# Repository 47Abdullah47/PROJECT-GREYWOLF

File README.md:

<h1 align="center">﷽</h1>
<h1 align="center">
<font size="6"><b>🛦 X-26 GREYWOLF PT-1</b></font>
</h1><br>

<h4 align="center">
  <b>The First High-Performance Experimental 12S EDF Prototype of the YF-26 GREYWOLF Program</b>
</h4>
<p align="center">
  <a href="#technical-specifications">Technical Specifications</a> •
  <a href="#visual-looks">Visual Looks</a> •
  <a href="#airframe-materials-list">Materials</a> •
  <a href="#electronics--propulsion-system">Electronics Strategy</a> •
  <a href="#system-wiring-diagram">Wiring Diagram</a> •
  <a href="#success-criteria--flight-goals">Flight Goals</a> •
  <a href="#assembly-guide">Assembly</a> •
  <a href="#credits">Credits</a> •
  <a href="#license">License</a>
</p>
<br>

> **Project Status:** Prototype 1 (PT-1) Engineering, Aerodynamic Simulation & CAD Phase Complete  
> **CAD Platform:** Autodesk Fusion 360  
> **Development Pipeline:** [Hack Club Stasis Dashboard](https://stasis.hackclub.com/dashboard/projects/cmnfqlx3300nv01qimu2rgsk3)  
> **Design Time Investment:** 50+ Hours of High-Fidelity Surface Modeling  
> **Source CAD File:** 💾 [Download Massive Fusion 360 (.f3d) Assembly via Google Drive](https://github.com/47Abdullah47/X-26-GREYWOLF-PT-1/blob/Main-Project-PT-1/SOURCE%20FILE.md)

---

## Technical Specifications

The **X-26 GREYWOLF PT-1** is a high-speed, scratch-built experimental scale RC jet aircraft. It is engineered around an advanced integrated propulsion duct system and a multi-axis high-lift control surface layout to study level transonic airflow behaviors, intake fluid dynamics, and low-altitude flight stability.

* **Total Length of Aircraft:** 1.3 - 1.5 meters
* **Total Height of Aircraft (without landing Gear):** 0.3m (~30cm)
* **Fuselage Hull Height:** 0.1m (~11cm) *(Optimized to wrap tightly around the internal engine bay)*
* **Wingspan:** ~1.0 meter
* **Wing Area:** ~0.1 m²
* **Total Control Channels:** 6 Channels (2x Flaps, 2x Ailerons, 2x Stabilators)
* **Aerodynamic Design & Fluid Optimization:** Validated via rigorous computational fluid dynamics (CFD) steady-state solver testing run at a 20 m/s airspeed vector, establishing a baseline cruise lift coefficient ($C_L$) of 0.0141 and an ultra-low geometric shape drag coefficient ($C_D$) of 0.0018.
* **Special Intake Engineering:** Features a custom-modeled internal S-Duct intake routing system designed to stabilize incoming air turbulence and manage static pressure gradients under high mass flows.
* **Performance Profile:** Estimated empty airframe weight ranges from 2.0 to 3.0 kg. Powered by a high-output 12S electric ducted fan producing between 4.0 - 5.0 kg of static thrust, yielding a >1:1 thrust-to-weight ratio for a flight envelope targeting 100 - 110 mph.
* **Short-Runway (STOL) Takeoff Speeds:**
  * *Unladen / Light Test Rig (3.5 kg):* 21.3 m/s - 23.0 m/s (~76 km/h)
  * *Maximum Operational Testing Payload (4.5 kg):* 24.6 m/s - 26.1 m/s (~94 km/h)
* **Control Surface Mixing:** Implements symmetrical **Flaperon** mixing, deflecting both flaps and main ailerons together at takeoff. This transforms **41.5% of the total wing area ($372.68\text{ cm}^2$)** into an active camber-shifting high-lift surface, rocketing the maximum takeoff lift coefficient ($C_{L_{\text{max}}}$) to approximately 0.165.

*Note: The structural frames, nose cone mechanics, and intake paths are modeled as completely independent components within the source assembly to allow for modular fabrication and fast battery bay accessibility.*

---

## Visual Looks

<h3 align="center"><b>CAD Model Overview</b></h3>
<p align="center">

  <a href="https://youtu.be/b9qI-MGt7ME"><b>A demonstration of the actuation of Control Surfaces</b></a>

</p>

<h3 align="center"><b>High-Fidelity Rendered Visuals</b></h3>

> **Design Note on Airframe Influence:** > The X-26 Greywolf airframe merges generation-defining design aspects. It utilizes high-efficiency forward intakes inspired by the F-22 Raptor, twin vertical stabilizing surfaces and an exhaust layout optimized similarly to the F-35 Lightning II, and an internal structural distribution derived from the F-16 Fighting Falcon. 

---

## Airframe Materials List

The structural framework utilizes a lightweight, high-strength composite prototyping approach to handle structural stress thresholds while maximizing the power-to-weight ratio:

1. **Depron Foam / High-Speed LW-PLA:** Used for the aerodynamic outer skin contours, wing surfacing, and lightweight internal fuselage formers.
2. **Carbon Fiber Spars & Rods (3mm):** Integrated directly into high-stress structural joints, serving as the main wing load spars, tail pivot shafts, and longitudinal fuselage stiffeners.
3. **Aircraft-Grade Plywood:** Selected for high-vibration structural hardpoints, specifically the main 12S EDF engine mount and landing gear mounting plates.

---

## Electronics & Propulsion Strategy

The PT-1's avionics bay is engineered to safely sustain high continuous current loads. Comprehensive component sourcing, unit prices, and specific funding breakdowns are tracked in the dedicated [Bill of Materials Guide](BOM.md).

### Power Architecture Summary:
1. **High-Voltage Power Loop:** Two independent 6S LiPo battery packs (5200mAh - 5900mAh) are linked in **series** using a heavy-duty **QS-8 Anti-Spark Series Harness** to deliver a unified 12S nominal voltage supply (44.4V nominal / 50.4V peak) directly to the ESC.
2. **Propulsion Drive Loop:** High-gauge phase leads feed directly from the Hobbywing 100A V2 ESC to the brushless motor inside the 80mm fan shroud.
3. **Low-Voltage Signal Loop:** Signal power to the 10-channel FlySky receiver steps down cleanly via the ESC's integrated Battery Eliminator Circuit (BEC) lines.
4. **Control Surface Actuation:** Symmetrical servos are linked across the receiver layout using heavy-duty Y-harness extensions to maintain precise dual-aileron, dual-flap, and stabilator mechanical sync.

---

## System Wiring Diagram

The PT-1 utilizes a clean point-to-point wiring schematic optimized for minimal line resistance and spatial balance within the narrow fuselage ribbing. 

---

## Success Criteria & Flight Goals

To rigorously evaluate the airframe engineering and telemetry code, the testing program focuses on three definitive goals:
1. **Aerodynamic Validation:** Confirm stable, level cruise tracking at a 20 m/s airspeed vector to ground-truth our baseline steady-state CFD dataset.
2. **STOL Performance:** Verify short-runway rotation and lift-off performance using the 41.5% trailing-edge flaperon configuration under incremental payload loads.

---

## Assembly Guide
The proper assembling procedure of the aircraft is as follows:-
<h3><b>THE SPINE</b></h3>
<p>The airduct of the plane has two major and very important roles in the aircraft, it serves as <b>THE SPINE</b> of the plane and the **The duct that** asissts the airflow.
It being <b>The Spine</b>  of the airplane, it will be the one hosting the airframe ribs.
</p>

<h3><b>Air-Frame Ribs Placement</b></h3>
<p>  The cuted out airframed ribs are slided onto the air duct, which is the spine of the aircraft. 
</p>

 <h3><b> First Skin Placement</b></h3>
 After sliding on the Airframe ribs onto the Airduct..The lower fuselage skin is mounted onto the airframe ribs.

<h3><b>Mounting Side panels</b></h3>
After mounting lower skin panel of the fuselage..the side skin panels are mounted onto the Airframe.

<h3><b>Adding support</b></h3>
3mm Carbon fibre rods are slided into the premade holes in airframes..the goal is to provide the airframe with a good tensile and torsion strength.
Also one of the rear support ribs are slided onto the carbin fibre rod for attatching to the main spine and be a part of the barrier against crushing G-force..Also the remaining side panels of the fuselage are mounted onto the rear support ribs.

<h3><b>Mounting Inner Skin Panels</b></h3>
Rear Inner skin panels are also mounted onto the rear support ribs.

<h3><b>Construction of the Stabs(stabilators)</b></h3>
The stab's construction is simple yet requires carefullness regarding the building process...The root aerofoil is mounted on the outer edges of the stab.

After mounting the root aerofoil on the root edge of lower skin panel of the stab...
the upper skin panel is mounted onto the root aerofoil and the corresponding outer edges of the lower skin panel....

After sucessfully mounting skin panels and the root aerfoil to eachother...the pivot rod is slided into the premade hole in the root aero foil.... 
The stabilators are done being built.

<h3><b>Mounting The Remaining Skin Panels</b></h3>
The remaing rear lower skin panels of the fuselage are also mounted onto the rear support ribs of the Fuselage..with the side skin panels supporting it.

After completing mounting the rear side of lower skin panels..The rear skin panels of the upper skin are also mounted onto the rear support ribs....

After mounting first rear skin panel of the upper skin...the second pair of skin panels are mounted onto the Airframe ribs...these two skin panels are directly sitting above the main propulsion unit of the UAV..

The side long skin panels are also mounted onto the Airframe ribs..these skin panels cover up the most of the Fuselage's upper skin....

The front upper skin panels of the Fuselage are mounted onto the front Airframe Ribs of the Airframe with the remaining upper side panels of the Airframe....the Cavity behind these panels is the space of the removeable panels that allow accessing the inner components of the Aircraft without needing to rip-apart the skin of the Aircraft.

A brief 3d view for the Construction described so far.
<video src="https://github.com/user-attachments/assets/6bf46d65-2bc3-4322-bec0-19ca2d736067" autoplay loop muted width="100%"></video>

<h3><b>Mounting Engine Nozzle</b></h3>
The Engine nozzle is consisted of 5 panels..the first three panels are mounted onto the correspeonding edges of the Inner side panels and Upper skin panels....

The fourth skin panel of the Engine nozzle is mounted onto the corresponding edges of the lower skin panel and onto the corresponding side edges of the second and thord side panels of the engnine side panels.

the last panel is the exhuast panel of the engine bay section, this can be replaced by a servo operated variable engine nozzle too, which is not the part of current development.

<h3><b>Installing the Nose ribs, nose panels, And completing the Fuselage</b></h3>
The Nose is installed by folowing a complex assembling procedure, the Battery block itself serves as a support, The two nose ribs are slided onto the carbon fibre rods, In this way the base of the nose is installed onto the Fuselage.

The lower nose skin panels are installed onto the assembled Structure of the Nose

After mounting the lower panels the side Skin panels are mounted onto the so far assembled nose strucutre.

After that The next Nose Rib is installed by three support brigdes,

After adding the next rib, the corresponding side Skin panels are mounted.

After mounting Side skin panels, the corresponding upper Skin panel is mounted 

after that, another Rib is added to the structure, and corresponding remaining side skin panels are mounted on, 

After that the last remaining upper skin panel is mounted.

THE DIVERGERS:-
The divergers are mounted on the tip of the lower intake Skin panel, Its purpose is to separate the low speed skin air from the high speed air,

After All of this process the Construction of the Fuselage is done.

<h3><b>Assembling the V-tails</b></h3>
The Ribs of the tails are mounted onto the one side of the Skins of the tail, 

After joining the Ribs with one skin, The other skin is mounted onto the ribs and the other skin,

Just like this the second tail is constructed, After joining skins and the ribs of the tail, the lower base root panel is mounted, sealing the whole structure,

After that carbon fibre support rods are slided into pre-built holes in the root panel,

This support rib is situated perpendicular to the actuator support of the STABS, its purpose is to lockin the Carbon fibre support Rods of the V-tails.

The Tails are slided into the Fuselage, Like This, (this is the inner view removing the outer skin panel from the vie)

And with that The V-tails are fused into the Fuselage.

<h3><b>Assembling the Wings</b></h3>
The front Ribs of the wing are fitted into the slots of the front spar, 

after fitting the ribs into the front spar, the main spar is slided onto the sleves of the ribs

After fitting the Main spar, the sleves of the Rear Ribs are slided into the main spar

the edge support ribs are then slided into gltye rear sleves of the rear ribs,

after that the Rear spar is fitted into the joint intersections made into the ribs and the spar.

After This step the Main Root aerofoil bulkhead is slided into the spar sleves to complete the structure of the removeable wings.

The two 5mm Carbon fibre rods are then slided into the holes and then locked using the collars inside the wings, so that the wings can be slides on and removed for easy transportation. 

The upper skin of 2mm depron is mounted onto the complex wing structure.

After mounting the upper depron skin, the lower depron skin is mounted to complete tge aerodynamic shape of the wing, also for servo fittings, there are pre cutout parts on the lower depron skin

And after that the sides of the wing, the "WING TIPS" are mounted on,

After mounting the wing tips, the
control surfaces "Flaps and Ailerons" are mounted onto the hinges that are fitted into the hinge support ribs, And the removeable wings are Completed

Now the 6mm wings' support bulkhead is installed into the airframe ribs and with the support rib similar to the root rib of the wing, enabling those two 5mm carbon fibre rods to be slided into the airframe,

This is how the Wing is installed, the carbon fibre rods are tightened up with the help of collars,

<h3><b>The Actuation Mechansim of Flaps and Ailerons</b></h3>
This is where the servos for Flaps and Ailerons go into the eing, and the actuation mechanism is shown perfectly below👇 

<h3><b>The Actuation Mechansim of the Stabilators</b></h3>
This is how the pushrods for the actuation of Stabilators reside,
a collar is installed onto the 3mm carbon fibre rod, that is connected to the stabilator, and the pushrod is used to rotate the collar which in turn, turns the rod, actuationg the stabilator

This is where the servo resides into the rear support ribs.

<h3><b>The Residence of The ESC</b></h3>
The esc is placed in the lower storage bay in the Airframe, that is near the lower skin panel and below the peak before dice of the Airduct.

<h3><b>Placement of the EDF</b></h3>
The EDF is placed onto the mounting brackets installed between the Airframe ribs, And is directly placed into the Airduct with the mouth directky attached to the exit of the Airduct to prevent any Airfeed Loss.
(The Air duct is hidden for a bteer view on the placement of the EDF)

<H3><B>Placement of the Reciever</B></H3>
The reciever/flight controller is placed in the upper storage bay that is direclty below the mid upper skin panel, The reason is to prevent any electrical noise from interfering with the reciver/FC, and for extending the antennas into carbon fibre free sections to prevent signal screening.

<h3>Placement of the batteries </h3>
The two 6s lipo packs are slided into the battery block that is also serving as the lower spine of the nose section, The block has cutouts on the upper sides to allow the wires to flow into the rear section of the UAV, and tye charging wires to be accessed easily.

<h4><b>THE END</b></h4>
And the Assembling process comes to an end. The product should,.must look like this

---

## Credits

* **My Father:** A seasoned professional in his aviation field who taught me the foundational mechanics of aircraft design, and inspired me to build this dream.
* **My Brother:** The catalyst who challenged me to test my limits, stepped up my design thinking, and introduced me to the open-source hardware community.
* **Hack Club Blueprint & Stasis Teams:** For establishing a development pipeline that empowers teenagers to scale up their hardware engineering skills and bring complex concepts to life.

---

## License

This project is open-source and licensed under the terms of the MIT License.

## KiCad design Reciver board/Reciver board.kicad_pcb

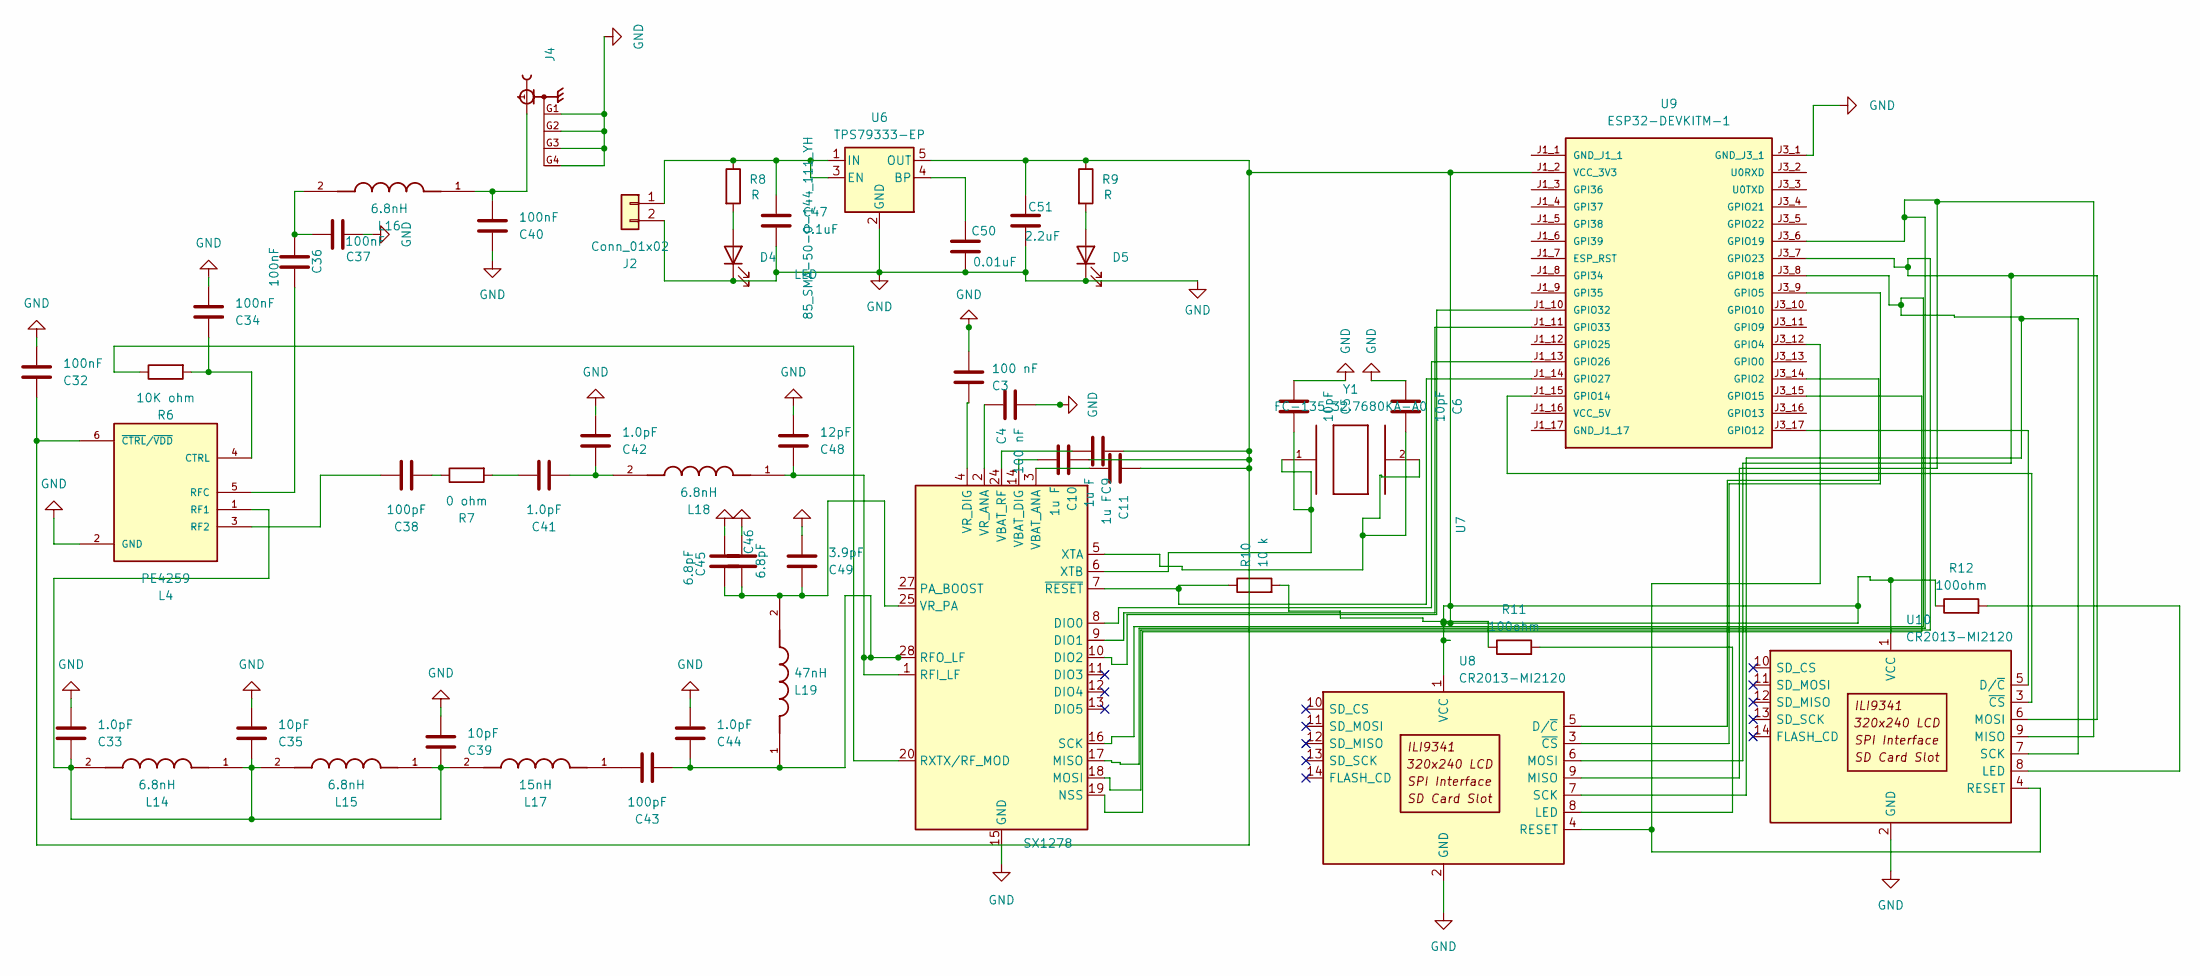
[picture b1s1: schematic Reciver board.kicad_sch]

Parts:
C3, C4: 100 nF; C_0201_0603Metric
C5: 10pF; C_0402_1005Metric
C6, C35, C39: 10pF; C_0201_0603Metric
C9, C10, C11: 1u F; C_0201_0603Metric
C32, C34, C36, C37, C40: 100nF; C_0201_0603Metric
C33, C41, C42, C44: 1.0pF; C_0201_0603Metric
C38, C43: 100pF; C_0201_0603Metric
C45, C46: 6.8pF; C_0201_0603Metric
C47: 0.1uF; C_0201_0603Metric
C48: 12pF; C_0201_0603Metric
C49: 3.9pF; C_0201_0603Metric
C50: 0.01uF; C_0201_0603Metric
C51: 2.2uF; C_0201_0603Metric
D4, D5: LED; LED_0805_2012Metric
J2: Conn_01x02; PinHeader_1x02_P2.54mm_Vertical
J4: 85_SMA-50-0-144_111_YH; HUBER_SUHNER_85_SMA-50-0-144_111_YH; PARTREV a
L4: PE4259; SOT65P215X110-6N
L14, L15, L16, L18: 6.8nH; IND_LQP03HQ10NH02D; PARTREV N/A
L17: 15nH; IND_LQP03HQ10NH02D; PARTREV N/A
L19: 47nH; IND_LQP03HQ10NH02D; PARTREV N/A
R6: 10K ohm; R_0201_0603Metric
R7: 0 ohm; R_0201_0603Metric
R8, R9: R; LED_0805_2012Metric
R10: 10 k; R_0201_0603Metric
R11, R12: 100ohm; R_0201_0603Metric
U6: TPS79333-EP; SOT-23-5
U7: SX1278; QFN-28-1EP_6x6mm_P0.65mm_EP4.8x4.8mm
U8, U10: CR2013-MI2120
U9: ESP32-DEVKITM-1; MODULE_ESP32-DEVKITM-1; PARTREV 1.0
Y1: FC-135_32.7680KA-A0; XTAL_FC-135_32.7680KA-A0

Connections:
GND: C3.2, C4.2, C5.1, C6.1, C32.2, C33.2, C34.2, C35.2, C37.2, C39.2, C40.1, C42.2, C44.2, C45.2, C46.2, C47.2, C48.2, C49.2, C50.2, C51.2, D4.1 (K), D5.1 (K), J2.2, J4.G1, J4.G2, J4.G3, J4.G4, L4.2 (GND), U6.2 (GND), U7.15 (GND), U7.21 (GND), U7.22 (GND), U7.23 (GND), U7.26 (GND), U7.29 (GND), U8.2 (GND), U9.J3_1 (GND_J3_1), U10.2 (GND)
unnamed: C36.2, C37.1, L16.2
unnamed: C38.2, R7.1
unnamed: C40.2, J4.1, L16.1
unnamed: C41.1, R7.2
unnamed: C41.2, C42.1, L18.2
unnamed: C43.1, L17.1
unnamed: D4.2 (A), R8.2
unnamed: D5.2 (A), R9.2
unnamed: C47.1, J2.1, R8.1, U6.1 (IN), U6.3 (EN)
unnamed: C34.1, L4.4 (CTRL), R6.2
unnamed: C33.1, C35.1, C39.1, L4.1 (RF1), L14.1, L14.2, L15.1, L15.2, L17.2
unnamed: C38.1, L4.3 (RF2)
unnamed: C36.1, L4.5 (RFC)
unnamed: C9.1, C10.1, C11.1, C32.1, C51.1, L4.6 (~CTRL/~VDD), R9.1, R10.2, R11.1, R12.1, U6.5 (OUT), U8.1 (VCC), U9.J1_2 (VCC_3V3), U10.1 (VCC)
unnamed: C50.1, U6.4 (BP)
unnamed: U7.8 (DIO0), U9.J1_13 (GPIO26)
unnamed: U7.9 (DIO1), U9.J1_11 (GPIO33)
unnamed: U7.10 (DIO2), U9.J1_10 (GPIO32)
unnamed: U7.19 (NSS), U9.J3_15 (GPIO15)
unnamed: C43.2, C44.1, C48.1, L18.1, L19.1, U7.1 (RFI_LF), U7.28 (RFO_LF)
unnamed: R6.1, U7.20 (RXTX/RF_MOD)
unnamed: C11.2, U7.3 (VBAT_ANA)
unnamed: C10.2, U7.14 (VBAT_DIG)
unnamed: C9.2, U7.24 (VBAT_RF)
unnamed: C4.1, U7.2 (VR_ANA)
unnamed: C3.1, U7.4 (VR_DIG)
unnamed: C45.1, C46.1, C49.1, L19.2, U7.25 (VR_PA)
unnamed: C6.2, U7.5 (XTA), Y1.2
unnamed: C5.2, U7.6 (XTB), Y1.1
unnamed: R10.1, U7.7 (~RESET), U9.J1_14 (GPIO27)
unnamed: U8.5 (D/~C), U9.J3_14 (GPIO2)
unnamed: R11.2, U8.8 (LED)
unnamed: U8.3 (~CS), U9.J3_9 (GPIO5)
unnamed: U9.J3_17 (GPIO12), U10.5 (D/~C)
unnamed: R12.2, U10.8 (LED)
unnamed: U7.17 (MISO), U8.9 (MISO), U9.J3_6 (GPIO19), U10.9 (MISO)
unnamed: U7.18 (MOSI), U8.6 (MOSI), U9.J3_7 (GPIO23), U10.6 (MOSI)
unnamed: U8.4 (RESET), U9.J3_12 (GPIO4), U10.4 (RESET)
unnamed: U7.16 (SCK), U8.7 (SCK), U9.J3_8 (GPIO18), U10.7 (SCK)
unnamed: U9.J1_15 (GPIO14), U10.3 (~CS)

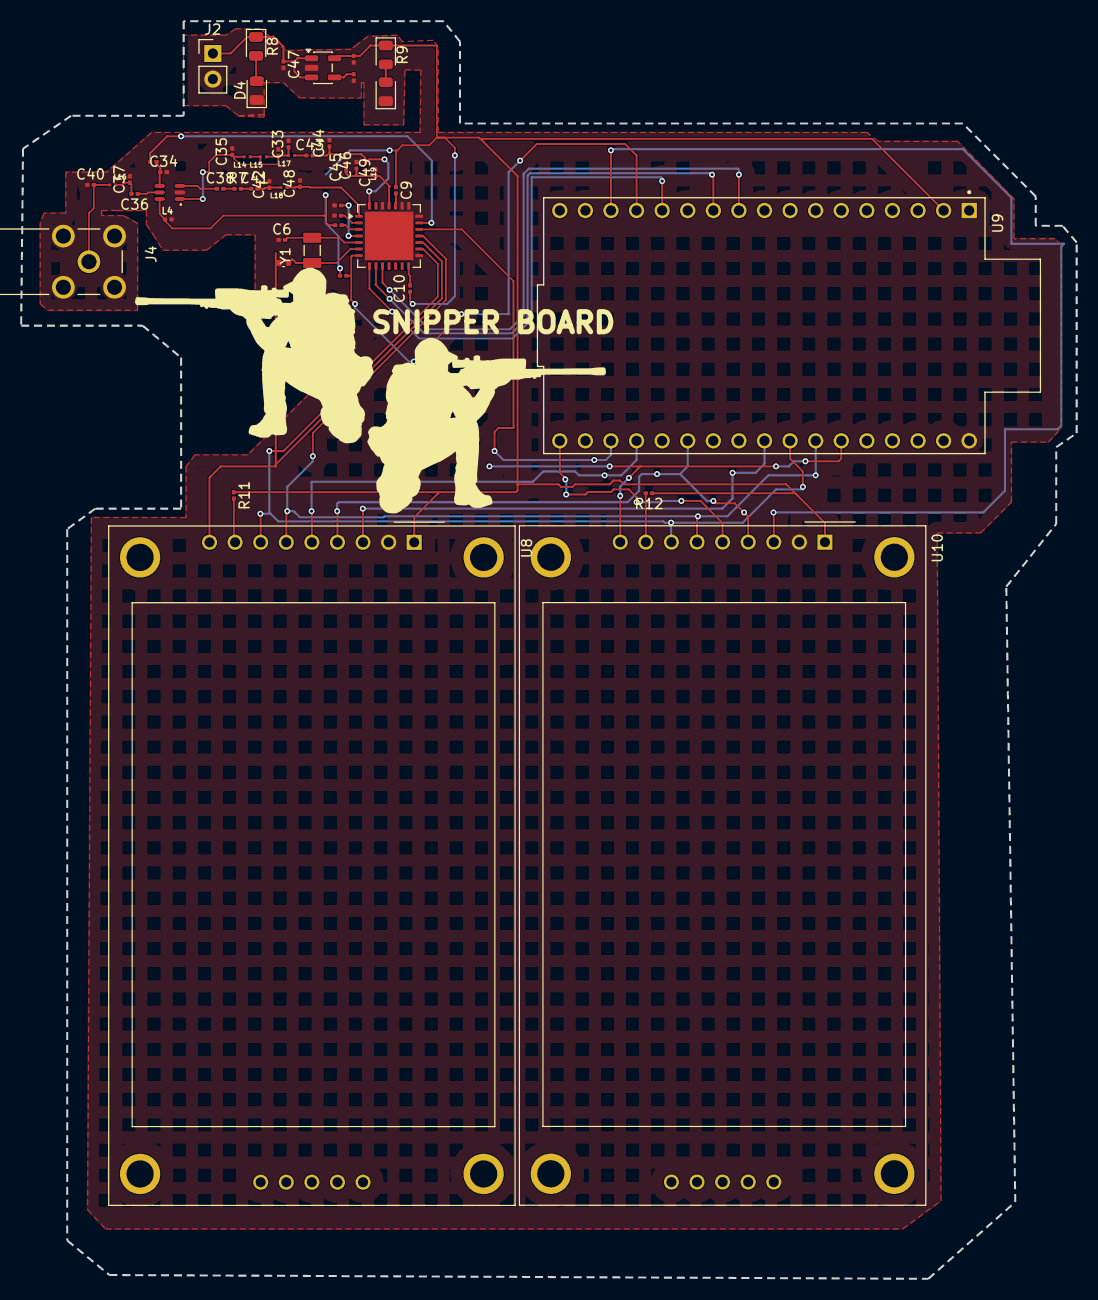
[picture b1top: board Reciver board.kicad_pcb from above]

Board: 2 copper layers, 104.8 x 124.8 mm, 51 parts (0 on the bottom side), 41 nets.

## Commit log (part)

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2026-01-23 Fix formatting and enhance receiver section in README
    Corrected formatting and improved clarity in the receiver section of the README.
2026-01-23 Fix formatting of RADAR section in README
2026-01-25 Update purchase notes and reimbursement details in BOM
2026-03-30 Update cost for 80mm Edf in Bill(BOM).csv
    Updated the cost of 80mm Edf and corrected the URL.
2026-04-01 Fix formatting and improve clarity in README
    Updated the README to correct formatting and improve clarity.
2026-04-01 Fix image link and improve README content
    Updated image link for Leopard V22 and made minor text corrections.
2026-04-10 Add new diagram and credits to README
    Updated the README with a new diagram and credits section.
2026-04-10 Fix typos in README and enhance credits section
    Corrected typos in the 'Writing Diagram' section and improved credit wording.
2026-04-22 Update README with printing cost considerations
    Added note about printing costs and material alternatives.
2026-04-23 Update Source files
2026-04-23 Update README with BOM and wiring diagram
    Added section for BOM and wiring diagram instructions.
2026-04-23 Modify Bill(BOM) with additional purchase links
    Updated item details and added links for purchases.
2026-04-23 Fix formatting in README table
2026-04-27 Revise build recommendations and remove 3D printing details
    Updated the recommendations for building the project, emphasizing the prototyping status and potential errors. Removed detailed 3D printing material suggestions and table for parts.
2026-05-28 Fix grammar and punctuation in README credits
    Corrected grammar and punctuation in the Credits section.
2026-06-30 Rename SOURCE FILE.F3D to SOURCE FILE.md

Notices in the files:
README.md:
License:
This project is open-source and licensed under the terms of the MIT License.
